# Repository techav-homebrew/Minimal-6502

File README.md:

# Minimal-6502
Minimal 6502 SBC based on Grant Searle's 8-chip 6502 computer and laid out as a 4x3" PCB.

Modifications from Grant Searle's design include:
- Addition of expansion header
- Changed clock from crystal to standard TTL can oscillator
- Added option for USB for serial & power via FTDI
- Reassembled software for 8kB EEPROM instead of 16kB EPROM because 27128 EPROM is not readily available (PCB still supports 27128)

## Assembly Notes
Part U5, 32kB SRAM, can be either a 7.5mm or 14.5mm width part. If using a 7.5mm package, it should be aligned as indicated on the side closest to the CPU. 

Computer can be assembled with either an RS-232 serial port for use with a traditional terminal or USB serial adapter for use with a modern computer as a terminal. Parts related to each option are listed below.

### RS-232 DE-9 Serial
- J1 - DE-9 connector
- U2 - MAX232 RS-232 level shifter
- C1, C2, C3, C4 - 100nF capacitor
- J3 - 2.1mm barrel power connector

### USB Serial
- J2 - USB-B connector
- U8 - FTDI FT230X
- R3, R4 - 26-Ohm resistor

## Usage Notes
The computer should be powered by USB or via the barrel connector, not both. There is no on-board voltage regulation, so if the barrel connector is used, then the computer should be powered by a regulated 5V power supply. 

Serial bit rate is 115200, and backspace should be configured for **Control-H** (PuTTY defaults to **Control-?**)

When using a terminal emulator via USB, it may be necessary to press Reset to display the Cold Start prompt. 

If no size is entered on the memory size prompt, then the computer will attempt to determine the installed memory size.

## Expansion Port Header Pinout
1. +5V
2. +5V
3. +5V
4. +5V
5. D0
6. A0
7. D1
8. A1
9. D2
10. A2
11. D3
12. A3
13. D4
14. A4
15. D5
16. A5
17. D6
18. A6
19. D7
20. A7
21. R/W#
22. A8
23. READ#
24. A9
25. WRITE#
26. A10
27. NMI#
28. A11
29. RDY
30. A12
31. IRQ#
32. A13
33. [Not Connected]
34. A14
35. Phi2
36. A15
37. Ground
38. Ground
39. Ground
40. Ground

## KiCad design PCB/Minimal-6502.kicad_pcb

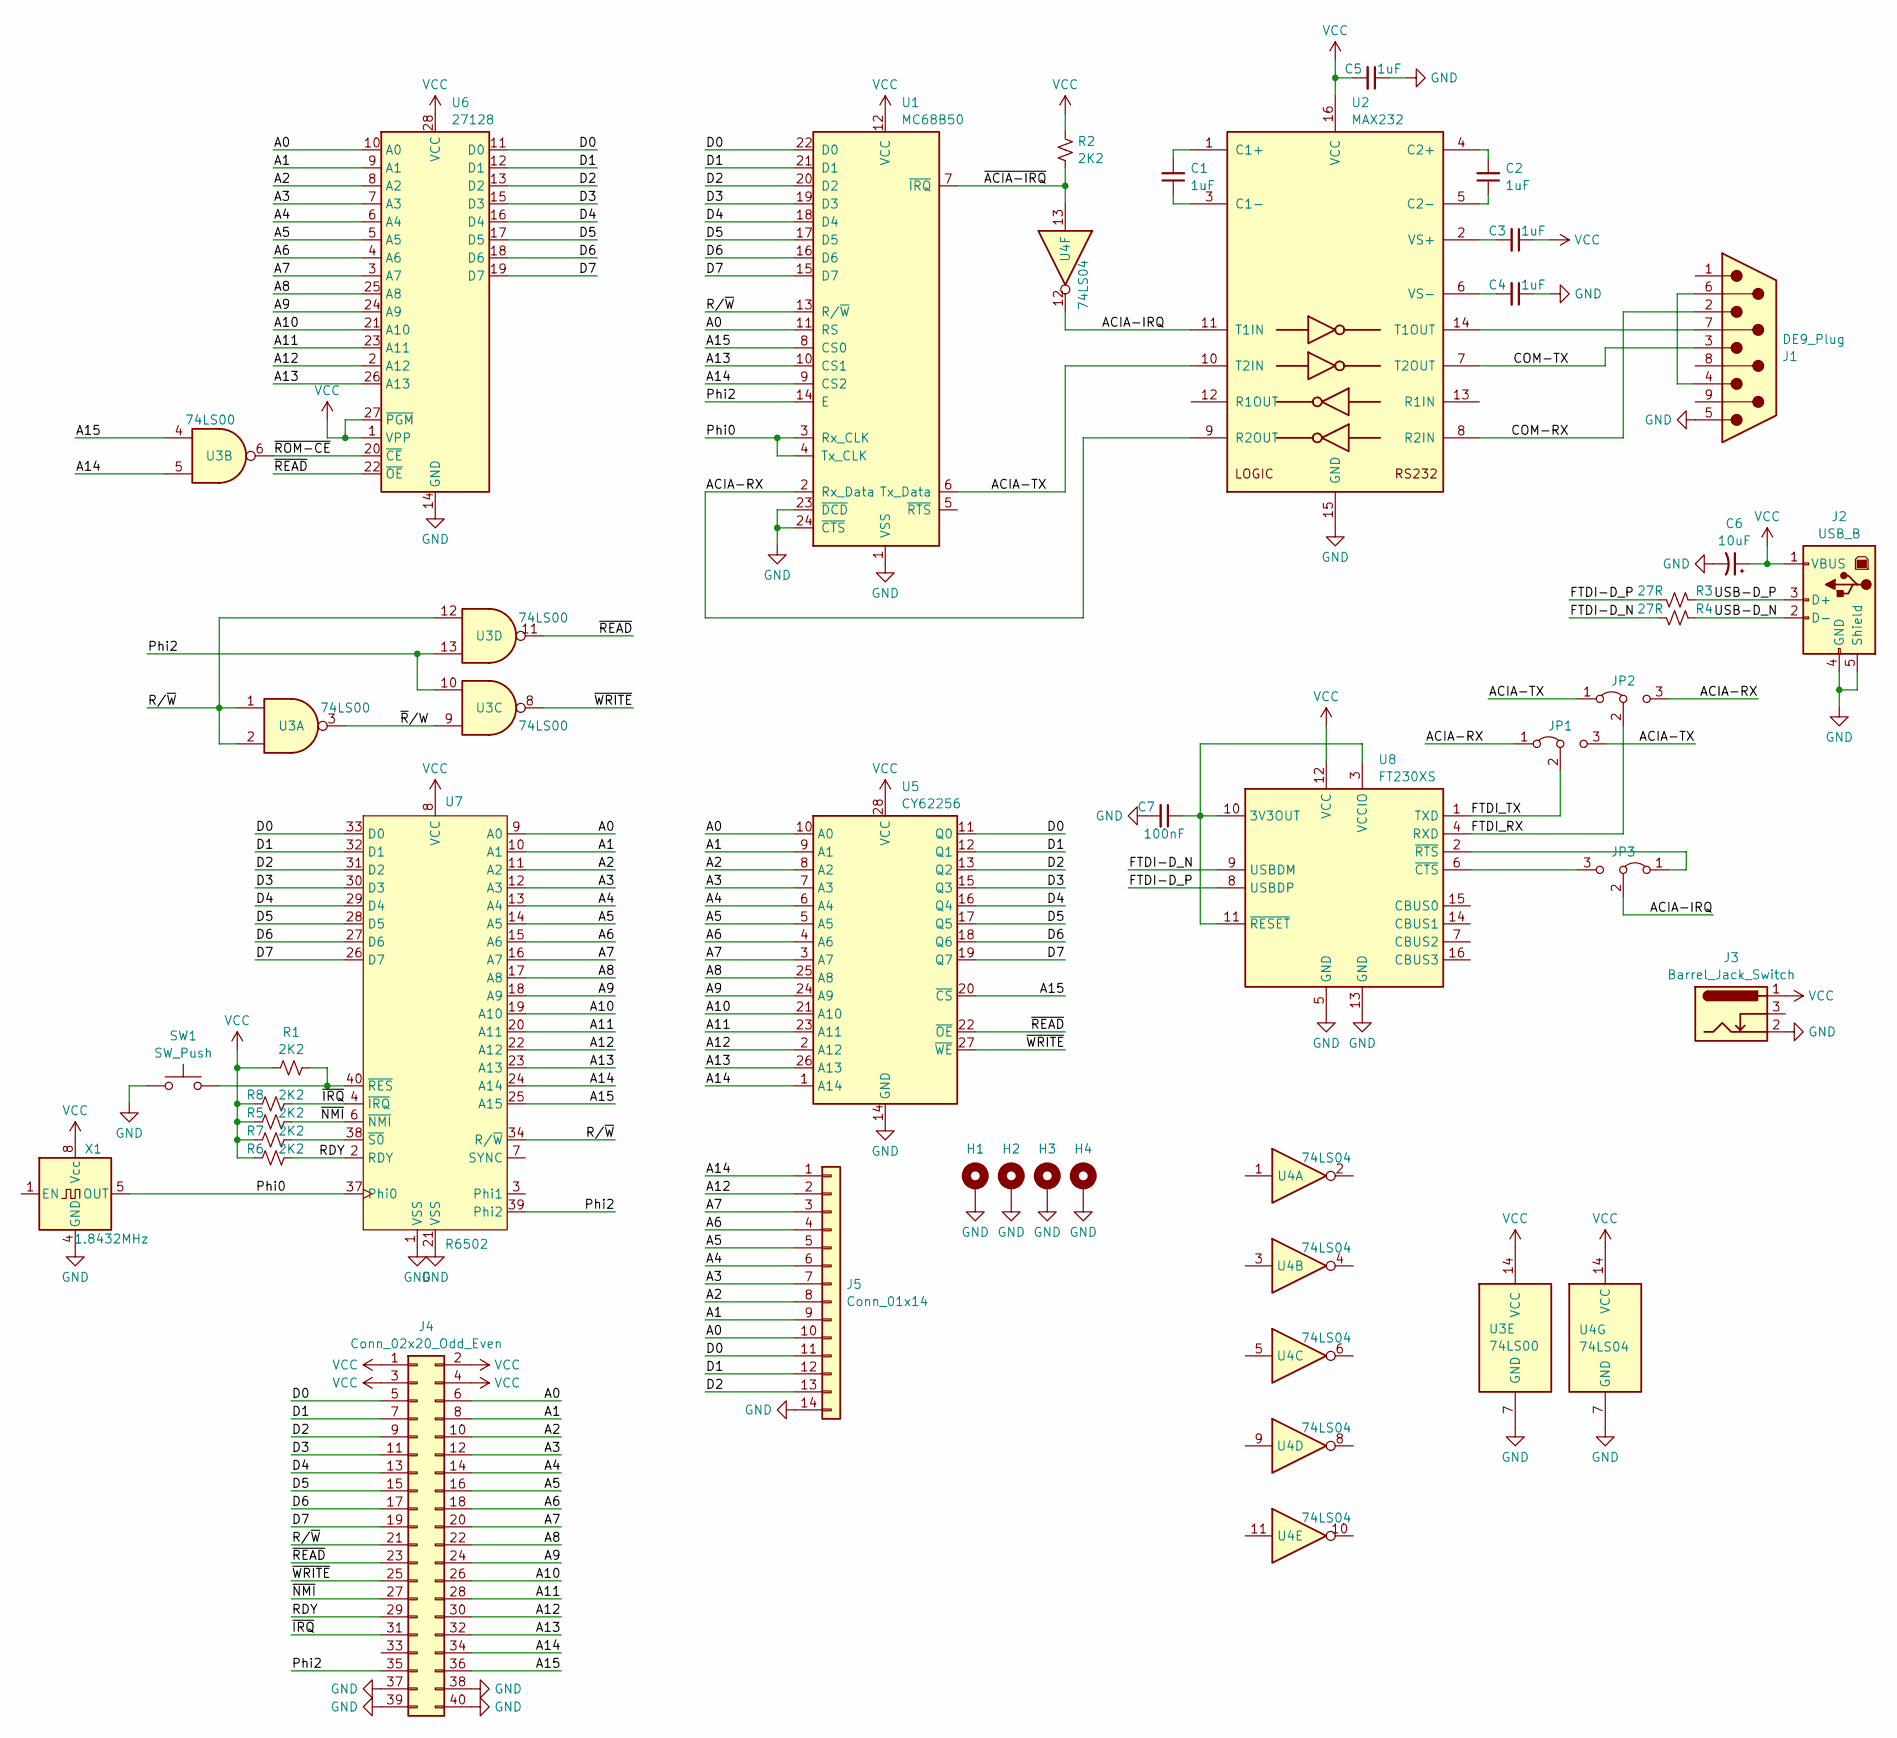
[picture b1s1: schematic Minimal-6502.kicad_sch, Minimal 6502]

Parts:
C1, C2, C3, C4, C5: 1uF; C_Disc_D5.0mm_W2.5mm_P2.50mm
C6: 10uF; CP_Radial_D8.0mm_P5.00mm
C7: 100nF; C_Disc_D5.0mm_W2.5mm_P2.50mm
H1, H2, H3, H4: MountingHole_Pad; MountingHole_3.2mm_M3_Pad_Via
J1: DE9_Plug; DSUB-9_Male_EdgeMount_P2.77mm
J2: USB_B; USB_B_OST_USB-B1HSxx_Horizontal
J3: Barrel_Jack_Switch; BarrelJack_Horizontal
J4: Conn_02x20_Odd_Even; PinHeader_2x20_P2.54mm_Horizontal
J5: Conn_01x14; PinHeader_1x14_P2.54mm_Vertical
JP1, JP2, JP3: Jumper_3_Bridged12; PinHeader_1x03_P2.54mm_Vertical
R1, R2, R5, R6, R7, R8: 2K2; R_Axial_DIN0207_L6.3mm_D2.5mm_P7.62mm_Horizontal
R3, R4: 27R; R_Axial_DIN0207_L6.3mm_D2.5mm_P7.62mm_Horizontal
SW1: SW_Push; SW_PUSH_6mm
U1: MC68B50; DIP-24_W15.24mm_Socket
U2: MAX232; DIP-16_W7.62mm_Socket
U3: 74LS00; DIP-14_W7.62mm_Socket
U4: 74LS04; DIP-14_W7.62mm_Socket
U5: CY62256; DIP-28_W15.24mm_Socket
U6: 27128; DIP-28_W15.24mm_Socket
U7: R6502; DIP-40_W15.24mm_Socket
U8: FT230XS; SSOP-16_3.9x4.9mm_P0.635mm
X1: 1.8432MHz; Oscillator_DIP-8

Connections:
/A0: J4.6, J5.10, U1.11 (RS), U5.10 (A0), U6.10 (A0), U7.9 (A0)
/A1: J4.8, J5.9, U5.9 (A1), U6.9 (A1), U7.10 (A1)
/A2: J4.10, J5.8, U5.8 (A2), U6.8 (A2), U7.11 (A2)
/A3: J4.12, J5.7, U5.7 (A3), U6.7 (A3), U7.12 (A3)
/A4: J4.14, J5.6, U5.6 (A4), U6.6 (A4), U7.13 (A4)
/A5: J4.16, J5.5, U5.5 (A5), U6.5 (A5), U7.14 (A5)
/A6: J4.18, J5.4, U5.4 (A6), U6.4 (A6), U7.15 (A6)
/A7: J4.20, J5.3, U5.3 (A7), U6.3 (A7), U7.16 (A7)
/A8: J4.22, U5.25 (A8), U6.25 (A8), U7.17 (A8)
/A9: J4.24, U5.24 (A9), U6.24 (A9), U7.18 (A9)
/A10: J4.26, U5.21 (A10), U6.21 (A10), U7.19 (A10)
/A11: J4.28, U5.23 (A11), U6.23 (A11), U7.20 (A11)
/A12: J4.30, J5.2, U5.2 (A12), U6.2 (A12), U7.22 (A12)
/A13: J4.32, U1.10 (CS1), U5.26 (A13), U6.26 (A13), U7.23 (A13)
/A14: J4.34, J5.1, U1.9 (CS2), U3.5, U5.1 (A14), U7.24 (A14)
/A15: J4.36, U1.8 (CS0), U3.4, U5.20 (~CS), U7.25 (A15)
/ACIA-IRQ: JP3.2 (C), U2.11 (T1IN), U4.12
/ACIA-RX: JP1.1 (A), JP2.3 (B), U1.2 (Rx_Data), U2.9 (R2OUT)
/ACIA-TX: JP1.3 (B), JP2.1 (A), U1.6 (Tx_Data), U2.10 (T2IN)
/COM-RX: J1.2, U2.8 (R2IN)
/COM-TX: J1.3, U2.7 (T2OUT)
/D0: J4.5, J5.11, U1.22 (D0), U5.11 (Q0), U6.11 (D0), U7.33 (D0)
/D1: J4.7, J5.12, U1.21 (D1), U5.12 (Q1), U6.12 (D1), U7.32 (D1)
/D2: J4.9, J5.13, U1.20 (D2), U5.13 (Q2), U6.13 (D2), U7.31 (D2)
/D3: J4.11, U1.19 (D3), U5.15 (Q3), U6.15 (D3), U7.30 (D3)
/D4: J4.13, U1.18 (D4), U5.16 (Q4), U6.16 (D4), U7.29 (D4)
/D5: J4.15, U1.17 (D5), U5.17 (Q5), U6.17 (D5), U7.28 (D5)
/D6: J4.17, U1.16 (D6), U5.18 (Q6), U6.18 (D6), U7.27 (D6)
/D7: J4.19, U1.15 (D7), U5.19 (Q7), U6.19 (D7), U7.26 (D7)
/FTDI-D_N: R4.1, U8.9 (USBDM)
/FTDI-D_P: R3.1, U8.8 (USBDP)
/FTDI_RX: JP2.2 (C), U8.4 (RXD)
/FTDI_TX: JP1.2 (C), U8.1 (TXD)
/Phi0: U1.3 (Rx_CLK), U1.4 (Tx_CLK), U7.37 (Phi0), X1.5 (OUT)
/Phi2: J4.35, U1.14 (E), U3.10, U3.13, U7.39 (Phi2)
/RDY: J4.29, R6.1, U7.2 (RDY)
/R/~W: J4.21, U1.13 (R/~W), U3.1, U3.2, U3.12, U7.34 (R/~W)
/USB-D_N: J2.2 (D-), R4.2
/USB-D_P: J2.3 (D+), R3.2
/~ACIA-IRQ: R2.2, U1.7 (~IRQ), U4.13
/~IRQ: J4.31, R8.1, U7.4 (~IRQ)
/~NMI: J4.27, R5.1, U7.6 (~NMI)
/~READ: J4.23, U3.11, U5.22 (~OE), U6.22 (~OE)
/~ROM-CE: U3.6, U6.20 (~CE)
/~R/W: U3.3, U3.9
/~WRITE: J4.25, U3.8, U5.27 (~WE)
GND: C4.1, C5.1, C6.2, C7.2, H1.1, H2.1, H3.1, H4.1, J1.5, J2.4 (GND), J2.5 (Shield), J3.2, J4.37, J4.38, J4.39, J4.40, J5.14, SW1.1, U1.1 (VSS), U1.23 (~DCD), U1.24 (~CTS), U2.15 (GND), U3.7 (GND), U4.7 (GND), U5.14 (GND), U6.14 (GND), U7.1 (VSS), U7.21 (VSS), U8.5 (GND), U8.13 (GND), X1.4 (GND)
unnamed: J1.4, J1.6
unnamed: JP3.1 (A), U8.2 (~RTS)
unnamed: JP3.3 (B), U8.6 (~CTS)
unnamed: C1.2, U2.1 (C1+)
unnamed: C1.1, U2.3 (C1-)
unnamed: C2.2, U2.4 (C2+)
unnamed: C2.1, U2.5 (C2-)
unnamed: J1.7, U2.14 (T1OUT)
unnamed: C3.2, U2.2 (VS+)
unnamed: C4.2, U2.6 (VS-)
unnamed: R1.1, SW1.2, U7.40 (~RES)
unnamed: R7.1, U7.38 (~S0)
unnamed: C7.1, U8.3 (VCCIO), U8.10 (3V3OUT), U8.11 (~RESET)
VCC: C3.1, C5.2, C6.1, J2.1 (VBUS), J3.1, J4.1, J4.2, J4.3, J4.4, R1.2, R2.1, R5.2, R6.2, R7.2, R8.2, U1.12 (VCC), U2.16 (VCC), U3.14 (VCC), U4.14 (VCC), U5.28 (VCC), U6.1 (VPP), U6.27 (~PGM), U6.28 (VCC), U7.8 (VCC), U8.12 (VCC), X1.8 (Vcc)

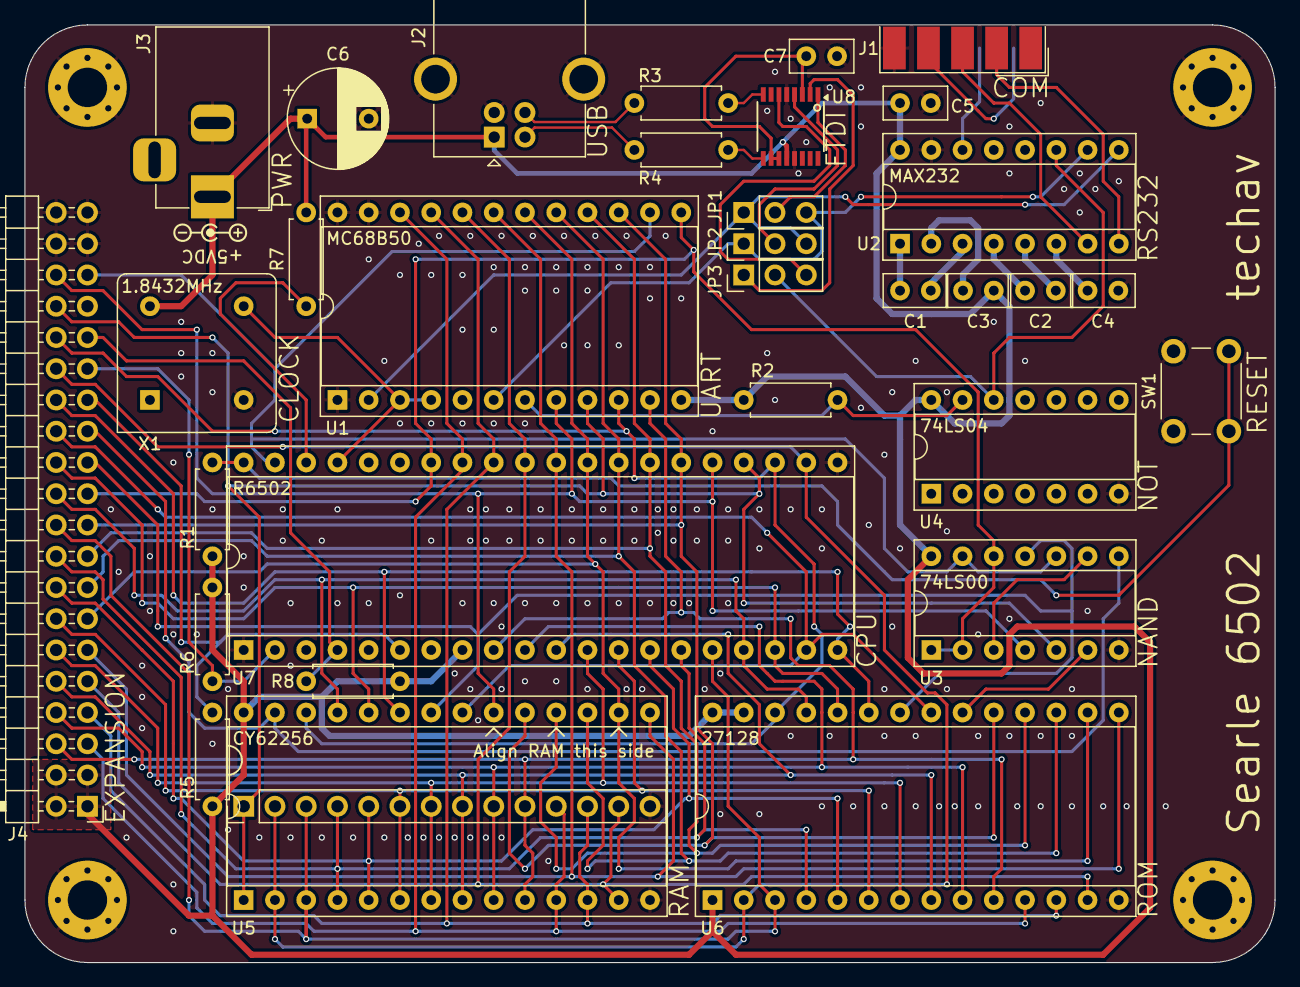
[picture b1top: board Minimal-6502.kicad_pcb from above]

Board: 2 copper layers, 101.6 x 76.2 mm, 37 parts (0 on the bottom side), 61 nets.

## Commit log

2024-05-27 Initial PCB
2024-06-11 Searle ROM code
2024-06-12 Target 8kB ROM
2024-06-12 Update documentation
